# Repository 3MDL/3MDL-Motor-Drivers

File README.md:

# About #

This repository contains design files for low-cost brushed DC motor drivers. These low-cost motor drivers were concieved for use in low-cost swarm robotics. Work was done under the Mechanism, Mobility, and Multifunctional Design Laboratory (3MDL) at the University of Toledo.

## In This Repository ##

The Firmware sub folder contains test code that was used to evaluate motor drivers that were based on microcontrollers.

The Hardware sub folder contains hardware design files for:
* An OP Amp based current regulator motor driver
    * This design was confirmed to work and the cost is marginally lower than the off the shelf driver IC solution. However, due to complex timing, only limited testing was performed before the motor driver failed due to shoot through in the H bridge circuit.
* A Microcrocontroller based current regulator motor driver
    * The footprint used for the microcntroller was incorrect so this design could not be evaluated
* A motor driver using an off the shelf motor driver IC
    * This design was confirmed to work, however near the current limit rating of the driver IC, additional cooling is required or else the driver IC goes into over temperature protection mode.

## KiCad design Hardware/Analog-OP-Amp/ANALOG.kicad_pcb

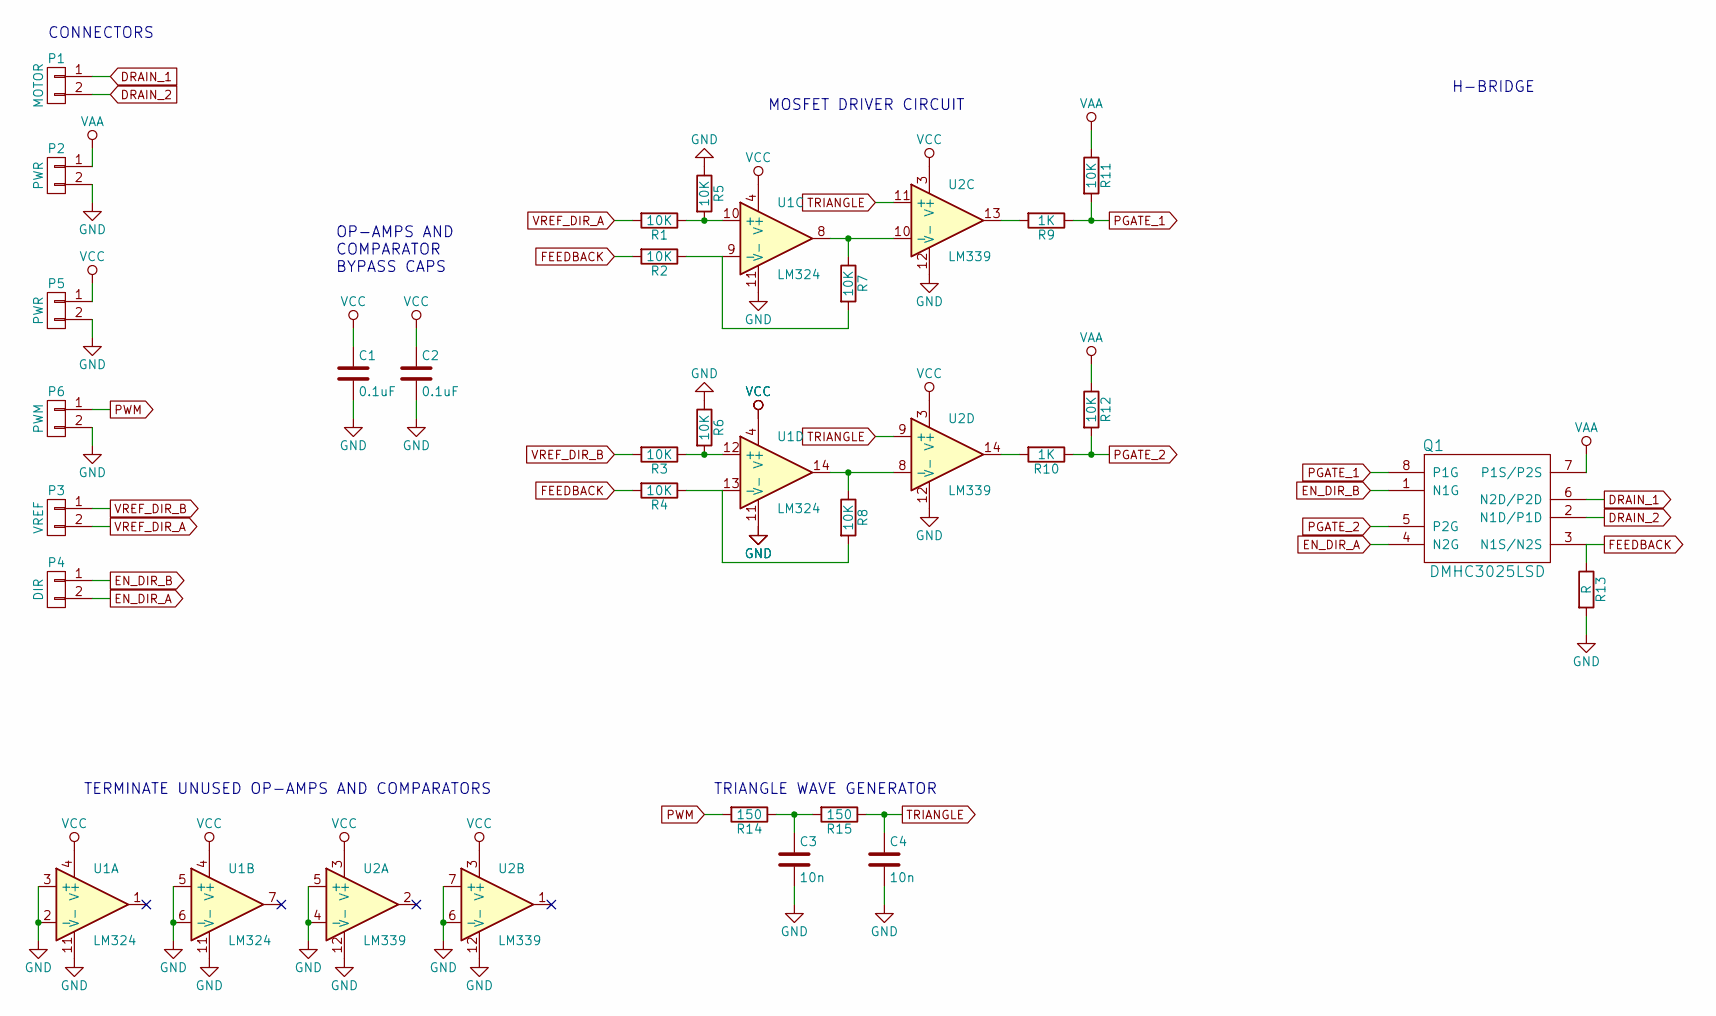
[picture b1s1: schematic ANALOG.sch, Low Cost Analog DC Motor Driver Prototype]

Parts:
C1, C2: 0.1uF; C_0603
C3, C4: 10n; C_0603
P1: MOTOR; 100MIL_ST
P2, P5: PWR; 100MIL_ST
P3: VREF; 100MIL_ST
P4: DIR; 100MIL_ST
P6: PWM; 100MIL_ST
Q1: DMHC3025LSD; SOIC-8_3.9x4.9mm_Pitch1.27mm
R1, R2, R3, R4, R5, R6, R7, R8, R11, R12: 10K; R_0603
R9, R10: 1K; R_0603
R13: R; R_1218
R14, R15: 150; R_0603
U1: LM324; SOIC-14_3.9x8.7mm_Pitch1.27mm
U2: LM339; SOIC-14_3.9x8.7mm_Pitch1.27mm

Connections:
DRAIN_1: P1.1, Q1.6 (N2D/P2D); also elsewhere on the board
DRAIN_2: P1.2, Q1.2 (N1D/P1D); also elsewhere on the board
EN_DIR_A: P4.2, Q1.4 (N2G); also elsewhere on the board
EN_DIR_B: P4.1, Q1.1 (N1G); also elsewhere on the board
FEEDBACK: Q1.3 (N1S/N2S), R2.2, R4.2, R13.1; also elsewhere on the board
GND: C1.2, C2.2, C3.2, C4.2, P2.2, P5.2, P6.2, R5.1, R6.1, R13.2, U1.2 (-), U1.3 (+), U1.5 (+), U1.6 (-), U1.11 (V-), U2.4 (-), U2.5 (+), U2.6 (-), U2.7 (+), U2.12 (V-)
unnamed: C3.1, R14.1, R15.2
unnamed: R1.1, R5.2, U1.10 (+)
unnamed: R2.1, R7.2, U1.9 (-)
unnamed: R3.1, R6.2, U1.12 (+)
unnamed: R4.1, R8.2, U1.13 (-)
unnamed: R7.1, U1.8, U2.10 (-)
unnamed: R8.1, U1.14, U2.8 (-)
unnamed: R9.2, U2.13
unnamed: R10.2, U2.14
PGATE_1: Q1.8 (P1G), R9.1, R11.2; also elsewhere on the board
PGATE_2: Q1.5 (P2G), R10.1, R12.2; also elsewhere on the board
PWM: P6.1, R14.2
TRIANGLE: C4.1, R15.1, U2.9 (+), U2.11 (+)
VAA: P2.1, Q1.7 (P1S/P2S), R11.1, R12.1; also elsewhere on the board
VCC: C1.1, C2.1, P5.1, U1.4 (V+), U2.3 (V+)
VREF_DIR_A: P3.2, R1.2
VREF_DIR_B: P3.1, R3.2

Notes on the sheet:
TERMINATE UNUSED OP-AMPS AND COMPARATORS
OP-AMPS AND COMPARATOR BYPASS CAPS
TRIANGLE WAVE GENERATOR
CONNECTORS
MOSFET DRIVER CIRCUIT
H-BRIDGE

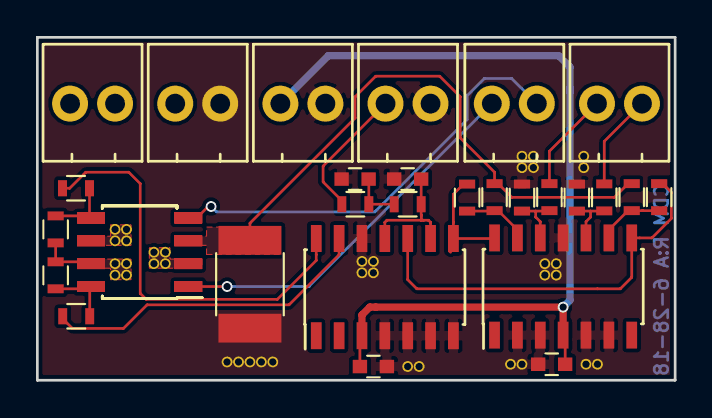
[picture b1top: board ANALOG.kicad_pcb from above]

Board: 2 copper layers, 35.4 x 19.0 mm, 30 parts (0 on the bottom side), 23 nets.

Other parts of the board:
Q1#2, Q1#3: DMHC3025LSD; SOIC-8_3.9x4.9mm_Pitch1.27mm

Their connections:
DRAIN_1: Q1#2.6, Q1#3.6; also elsewhere on the board
DRAIN_2: Q1#2.2, Q1#3.2; also elsewhere on the board
EN_DIR_A: Q1#2.4, Q1#3.4; also elsewhere on the board
EN_DIR_B: Q1#2.1, Q1#3.1; also elsewhere on the board
FEEDBACK: Q1#2.3, Q1#3.3; also elsewhere on the board
PGATE_1: Q1#2.8, Q1#3.8; also elsewhere on the board
PGATE_2: Q1#2.5, Q1#3.5; also elsewhere on the board
VAA: Q1#2.7, Q1#3.7; also elsewhere on the board

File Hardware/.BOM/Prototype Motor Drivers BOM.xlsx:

Designation | Kicad Package | Quantity | Digikey PN
0.05 Ohm Resistor | R_1812 | 10 | P50NBCT-ND
150 Ohm Resistor | R_0603 | 10 | RNCP0603FTD150RCT-ND
22pF Ceramic Capacitor | C_0603 | 10 | 732-7748-1-ND
10n Ceramic Capacitor | C_0603 | 10 | 732-7933-1-ND
0.1u Ceramic Capacitor | C_0603 | 10 | Can’t Find
47u Electrolytic Capacitor | CP_Elec_6.3x7.7 | 3 | PCE3908CT-ND
DMHC3025LSD MOSFET (H-Bridge) | SOIC-8_3.9x4.9mm_Pitch1.27mm | 10 | DMHC3025LSD-13DICT-ND
Q_NMOS_DGS MOSFET (NMOS) | SOT-23 | 10 | 2N7002-FDICT-ND
DRV8870 Motor Driver | HTSOP-8-1EP_3.9x4.9mm_Pitch1.27mm | 3 | 296-42660-1-ND
LM324 OP-Amp | SOIC-14_3.9x8.7mm_Pitch1.27mm | 3 | 497-1580-1-ND
LM339 Comparator | SOIC-14_3.9x8.7mm_Pitch1.27mm | 3 | 296-1013-1-ND
ATTINY24A-M Microcontroller | QFN-24-1EP_4x4mm_Pitch0.5mm | 3 | ATTINY24A-MURCT-ND

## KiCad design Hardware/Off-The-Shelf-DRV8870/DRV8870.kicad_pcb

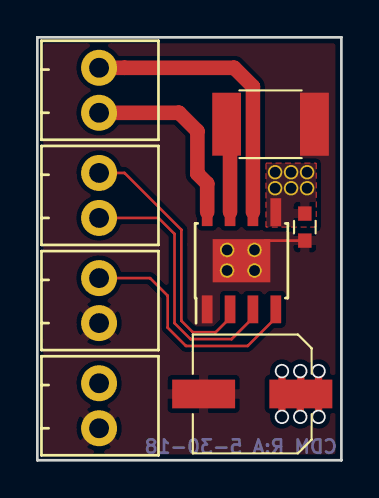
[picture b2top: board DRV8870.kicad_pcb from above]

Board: 2 copper layers, 16.9 x 23.5 mm, 8 parts (0 on the bottom side), 8 nets.

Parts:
C1: 47u; CP_Elec_6.3x7.7
C2: 0.1u; C_0603
P1: PWR; 100MIL_ST
P2: DIR; 100MIL_ST
P3: VREF; 100MIL_ST
P4: MOTOR; 100MIL_ST
R1: 0.1; R_1812
U1: DRV8870; HTSOP-8-1EP_3.9x4.9mm_Pitch1.27mm

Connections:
GND: C1.2, C2.1, P1.2, P3.2, R1.2, U1.1, U1.9
IN1: P2.2, U1.3
IN2: P2.1, U1.2
unnamed: R1.1, U1.7
OUT1: P4.1, U1.6
OUT2: P4.2, U1.8
VCC: C1.1, C2.2, P1.1, U1.5
VREF: P3.1, U1.4

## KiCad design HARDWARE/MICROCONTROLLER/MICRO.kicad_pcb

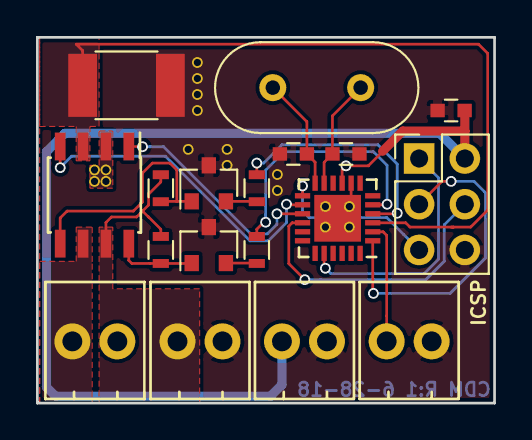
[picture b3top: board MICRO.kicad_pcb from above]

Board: 2 copper layers, 25.4 x 20.3 mm, 18 parts (0 on the bottom side), 21 nets.

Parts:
C1: 0.1uF; C_0603
C2, C3: 22pF; C_0603
IC1: ATTINY24A-M; QFN-24-1EP_4x4mm_Pitch0.5mm
P1: MOTOR; 100MIL_ST
P2: VREF; 100MIL_ST
P3, P4: POWER; 100MIL_ST
P5: ICSP; Pin_Header_Straight_2x03_Pitch2.54mm
Q1: DMHC3025LSD; SOIC-8_3.9x4.9mm_Pitch1.27mm
Q2, Q3: Q_NMOS_DGS; SOT-23
R1, R3, R4, R5: 1K; R_0603
R2: R; R_1812
Y1: Crystal; Crystal_HC49-U_Vertical

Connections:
FEEDBACK: IC1.3, Q1.3, R2.1
GND: C1.2, C2.1, C3.1, IC1.8, P2.2, P3.2, P4.2, P5.6, Q2.3, Q3.3, R2.2
MISO: IC1.20, P5.1
MOSI: IC1.16, P5.4
N1G: IC1.15, Q1.1
N2G: IC1.14, Q1.4
unnamed: C2.2, IC1.11, Y1.2
unnamed: C3.2, IC1.12, Y1.1
unnamed: Q1.5, Q3.1, R5.2
unnamed: Q1.8, Q2.1, R1.2
unnamed: Q2.2, R3.1
unnamed: Q3.2, R4.1
OUT_A: P1.1, Q1.6
OUT_B: P1.2, Q1.2
P1G: IC1.5, R3.2
P2G: IC1.4, R4.2
RST: IC1.13, P5.5
SCK: IC1.1, P5.3
VAA: P3.1, Q1.7, R1.1, R5.1
VCC: C1.1, IC1.9, P4.1, P5.2
VREF: IC1.2, P2.1

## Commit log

2018-07-02 initial
2019-03-08 restructuring
2019-03-08 readme
2019-03-08 removed readme
